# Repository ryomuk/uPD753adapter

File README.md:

# uPD753adapter
Adapter for NEC uPD753 to convert to Intel 8080 pinout.

## 概要
- NEC uPD753を8080のピン配列にするためのアダプタです．

## 基板

- 実物

### BOM
|Reference          |Qty| Value          |Memo |
|-------------------|---|----------------|-----|
|C1,C2              |2  |0.1uF           |     |
|J1                 |1  |42pin ZIF Socket|uPD753用ソケット |
|J2                 |1  |40pinの何か     |8080側端子 |

## 動作例
- [TangNano8080MEM](https://github.com/ryomuk/tangnano-5V/tree/main/applications/TangNano8080MEM)に載せてみたところ，問題無く動作しました．

## 関連情報
- uCOM-8 [www.st.rim.or.jp/~nkomatsu/nec/uPD753.html](http://www.st.rim.or.jp/~nkomatsu/nec/uPD753.html)
- NEC μCOMシリーズ総合ユーザーズガイド 1978 SUMMER pp.32-33

## 更新履歴
- 2024/09/09: 初版公開

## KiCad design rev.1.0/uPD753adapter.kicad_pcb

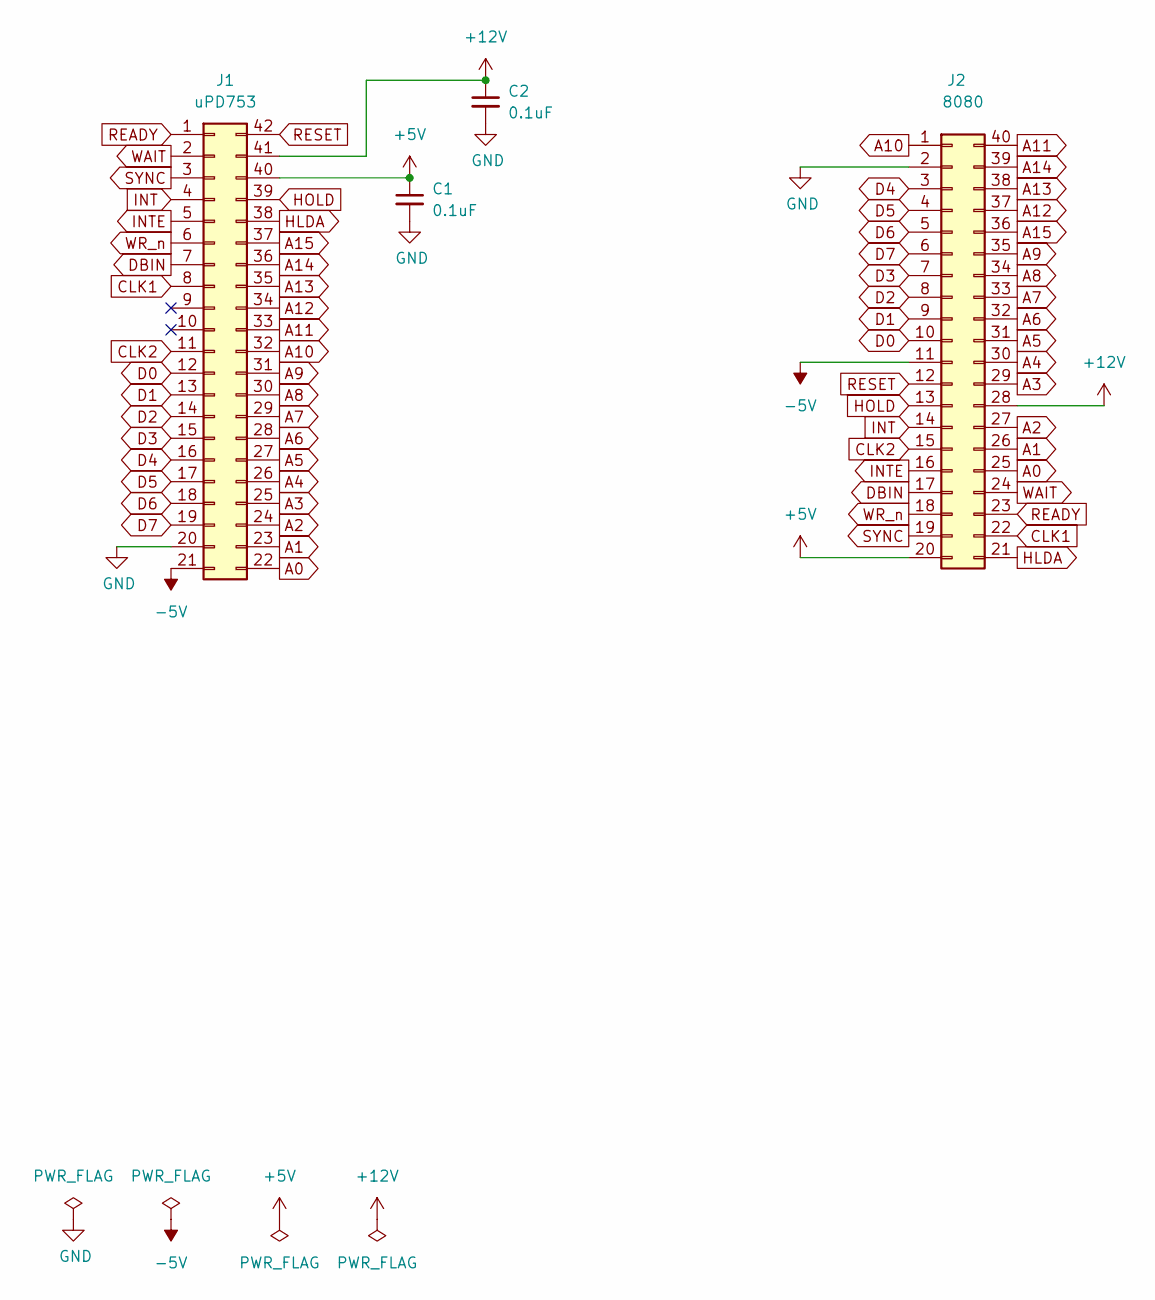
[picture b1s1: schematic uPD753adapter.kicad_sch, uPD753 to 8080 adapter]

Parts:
C1, C2: 0.1uF; C_Disc_D5.0mm_W2.5mm_P2.50mm
J1: uPD753; DIP_Socket-42_W11.9_W12.7_W15.24_W17.78_W18.5_3M_242-1281-0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
J2: 8080; DIP-40_W15.24mm_Socket

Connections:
+5V: C1.1, J1.40, J2.20
+12V: C2.1, J1.41, J2.28
-5V: J1.21, J2.11
A0: J1.22, J2.25
A1: J1.23, J2.26
A2: J1.24, J2.27
A3: J1.25, J2.29
A4: J1.26, J2.30
A5: J1.27, J2.31
A6: J1.28, J2.32
A7: J1.29, J2.33
A8: J1.30, J2.34
A9: J1.31, J2.35
A10: J1.32, J2.1
A11: J1.33, J2.40
A12: J1.34, J2.37
A13: J1.35, J2.38
A14: J1.36, J2.39
A15: J1.37, J2.36
CLK1: J1.8, J2.22
CLK2: J1.11, J2.15
D0: J1.12, J2.10
D1: J1.13, J2.9
D2: J1.14, J2.8
D3: J1.15, J2.7
D4: J1.16, J2.3
D5: J1.17, J2.4
D6: J1.18, J2.5
D7: J1.19, J2.6
DBIN: J1.7, J2.17
GND: C1.2, C2.2, J1.20, J2.2
HLDA: J1.38, J2.21
HOLD: J1.39, J2.13
INT: J1.4, J2.14
INTE: J1.5, J2.16
READY: J1.1, J2.23
RESET: J1.42, J2.12
SYNC: J1.3, J2.19
WAIT: J1.2, J2.24
WR_n: J1.6, J2.18

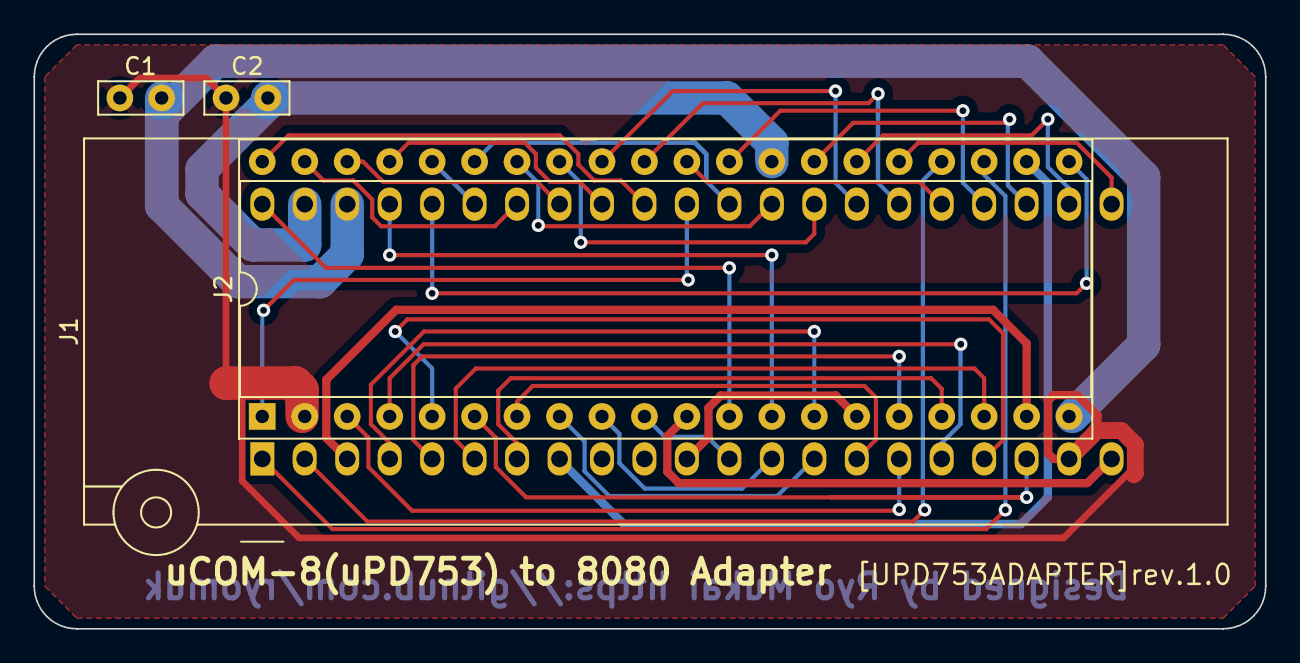
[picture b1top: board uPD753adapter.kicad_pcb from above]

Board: 2 copper layers, 73.7 x 35.6 mm, 4 parts (0 on the bottom side), 40 nets.
